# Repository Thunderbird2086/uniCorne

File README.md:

# uniCorne

uniCorne is inspired by [corne](foostatn/crkbd), and here are the key features of uniCorne:

1. **Controller Compatibility**: uniCorne is specifically tailored to work with ProMicro-like controllers such as [Nice!Nano](https://nicekeyboards.com/docs/nice-nano/), [Elite-Pi](https://docs.keeb.io/elite-pi-guide), and [Ble Micro Pro](https://sekigon-gonnoc.github.io/BLE-Micro-Pro/#/). This ensures seamless integration and optimal performance.
1. **Hardware Handedness**: Unlike many other keyboards, uniCorne supports hardware handedness for ProMicro-like RP2040 controller boards. This flexibility allows users to choose their preferred orientation without sacrificing functionality.
1. **Nice!View Integration**: uniCorne has been meticulously crafted to seamlessly integrate with [Nice!View](https://nicekeyboards.com/docs/nice-view/). Users can enjoy a cohesive experience without needing any modifications to the board.

In summary, uniCorne combines controller compatibility, hardware flexibility, and thoughtful integration, making it a standout choice for keyboard enthusiasts.

## Profiles
uniCorne offers three distinct flavors: standard profile, low profile, and hybrid profile.

### Standard Profile
Equipped with Cherry MX compatible switches, available in both 3-pin and 5-pin.<br>

### Low Profile
The low-profile variant primarily incorporates Kailh Low-Profile switches, supporting both Kailh Choc V1 and V2 switches.<br>

### Hybrid Profile
In the hybrid setup, low-profile switches are utilized for the thumb block, while standard-profile switches are employed for the remaining keys.<br>

## Variants
uniCorne is availabe in two enticing variations: 3x5 and 3x6.

The 3x6 variant caters to users who may not be accustomed to split keyboards, as its layout closely resembles that of standard keyboards. With 21 keys on each side, the 3x6 configuration boasts a total of 42 keys.<br>

On the other hand, the 3x5 variant provides a more streamlined option, with 18 keys on each side for a total of 36 keys.

## Build Guides
uniCorne 3x5 is used as an example. Refer to [the guides](https://thunderbird2086.github.io/uniCorne).

## fonts
 - [Android Robot](https://www.1001freefonts.com/android-robot.font)
 - [Avenir Next Heavy](https://en.maisfontes.com/avenir-next-heavy.font)
 - [Hack](https://www.1001freefonts.com/hack.font)

## firmwares
 - [QMK](https://github.com/Thunderbird2086/tb2086-qmk)
 - [ZMK](https://github.com/Thunderbird2086/unicorne-zmk-config)

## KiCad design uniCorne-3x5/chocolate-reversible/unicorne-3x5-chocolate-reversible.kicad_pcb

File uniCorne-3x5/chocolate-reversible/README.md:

# uniCorne 3x5 Low Profile

## Top

## Bottom

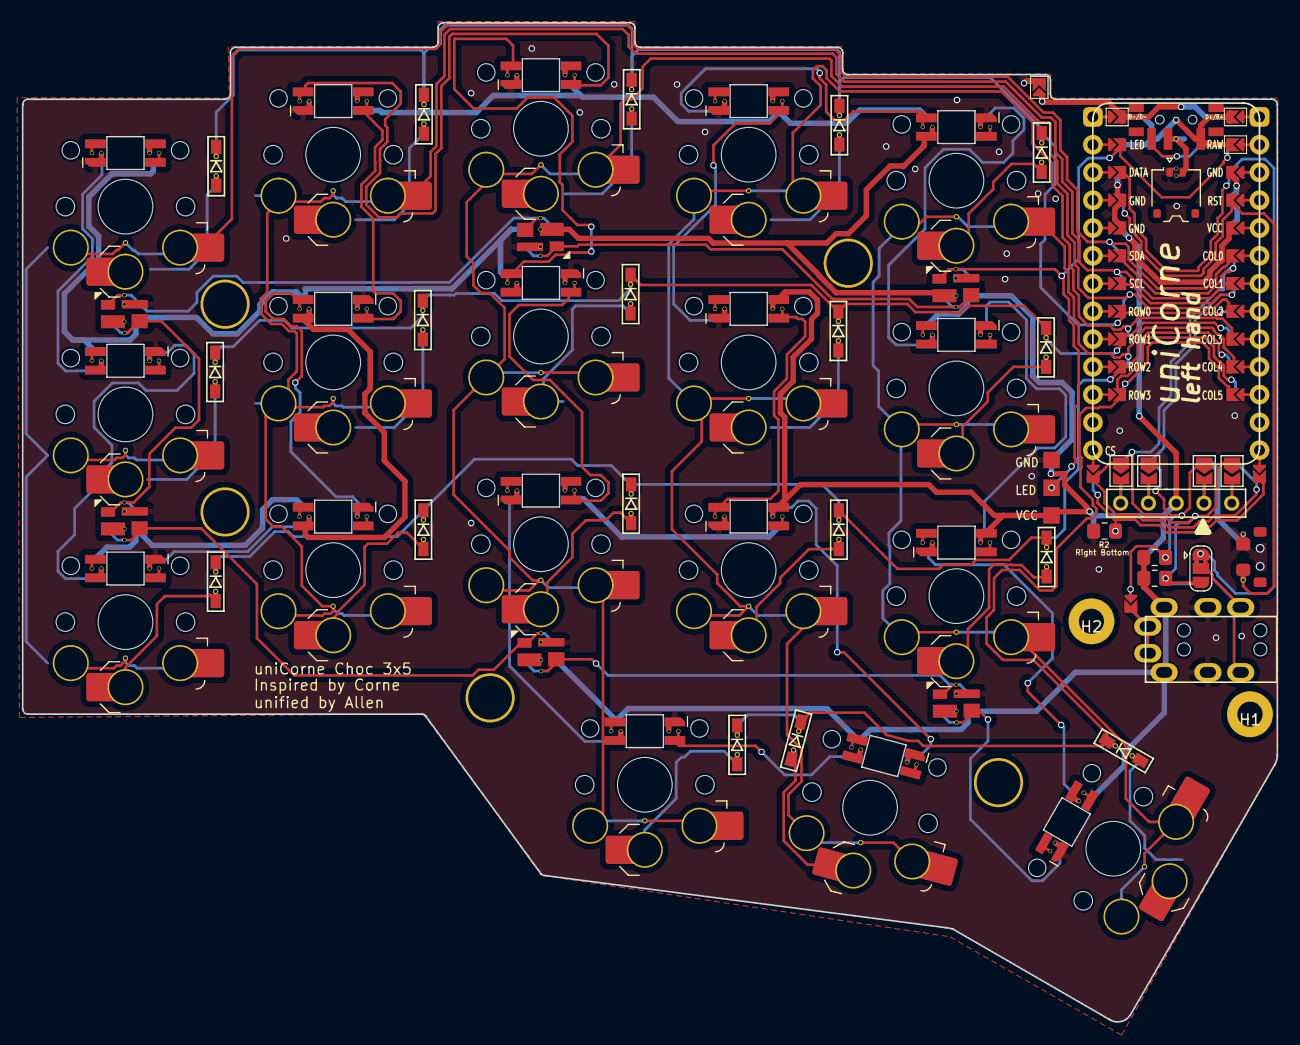
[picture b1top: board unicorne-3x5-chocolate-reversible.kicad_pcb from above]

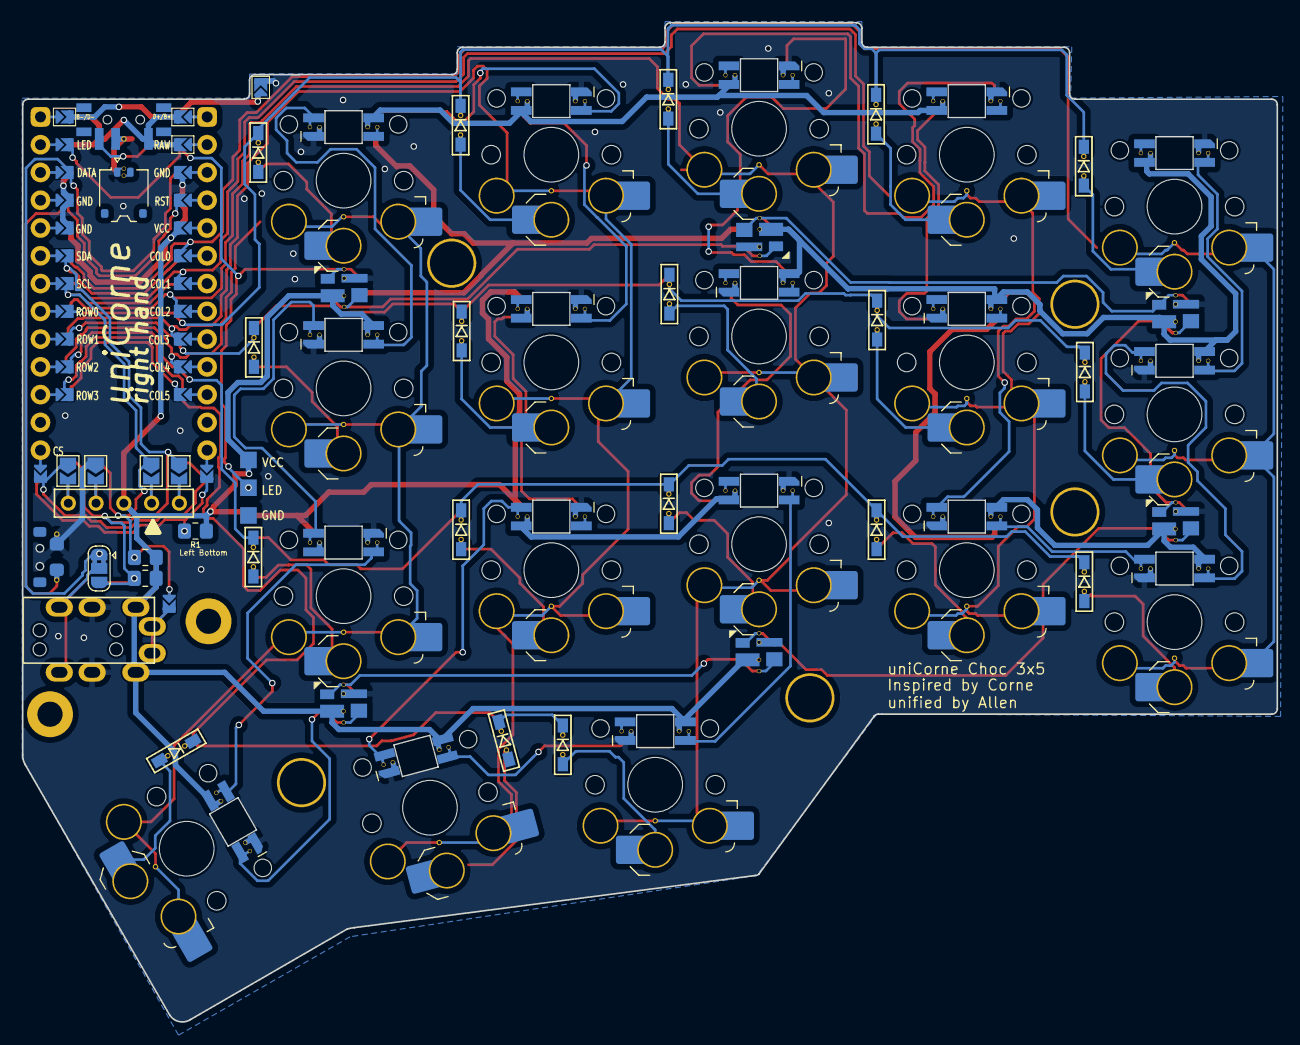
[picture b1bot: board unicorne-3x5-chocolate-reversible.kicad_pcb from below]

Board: 2 copper layers, 114.7 x 91.4 mm, 89 parts (30 on the bottom side), 68 nets.

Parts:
D1, D2, D3, D4, D5, D6, D7, D8, D9, D10, D11, D12, D13, D14, D15, D16, D17, D18: D; D3_SMD_rev
H1, H2: MountingHole; M2_Hole_TH
H3, H4, H5, H6, H7: MountingHole; M2_Hole_TH_Outside
J1: MJ-4PP-9; TRRS-PJ-320A-rev
J2: Conn_01x05; Nice!View
J3: Conn_01x02; Molex_Pico-EZmate_78171-0002_1x02-1MP_P1.20mm_Vertical_rev
J4: Conn_01x03; StripLED_rev
JP1, JP2, JP3, JP4, JP5, JP6, JP7, JP8: Jumper_2_Open; SolderJumper-2_P1.3mm_Open_TrianglePad1.0x1.5mm
JP9: Jumper_3_Bridged12; SolderJumper-3_P1.3mm_Bridged2Bar12_RoundedPad1.0x1.5mm_rev
JP10, JP11: SolderJumper-2_P1.3mm_Open_TrianglePad1.0x1.2mm_rev
L1, L2, L3, L4, L5, L6, L7, L8, L9, L10, L11, L12, L13, L14, L15, L16, L17, L18: SK6812MINI-E; LED_SK6812MINI-E_rev
L19, L20, L21, L22, L23, L24: SK6812MINI; LED_SK6812MINI_PLCC4_3.5x3.5mm_P1.75mm_rev_all
PSW1: SW_SPDT; SW_SPDT_PCM12_reversible
R1, R2: 10k; R_0805_2012Metric_Pad1.20x1.40mm_HandSolder
R3, R4: 4.7k; R_0805_2012Metric_Pad1.20x1.40mm_HandSolder_rev
RSW1: SMT 2X4X3.5MM Tactile Tact Push Button; SMT 2X4X3.5MM Tactile Tact Push Button rev
SW1, SW2, SW3, SW4, SW5, SW6, SW7, SW8, SW9, SW10, SW11, SW12, SW13, SW14, SW15, SW16, SW17: SW_CHOC_HS; SW_choc_v1_v2_HS_1u_reversible
SW18: SW_CHOC_HS; SW_choc_v1_v2_HS_1.5u_reversible
U1: ProMicro-ish; ProMicro-ish-dn-rev-unrouted_3x5

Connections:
B-/D-: JP11.1 (A), U1.26 (B-/D-)
BAT+: PSW1.1 (A), U1.24 (RAW), U1.25 (D+/B+)
CS: JP1.1 (A), JP8.1 (A), U1.12 (B5)
DATA: JP9.1 (A), U1.2 (RX)
GND: J1.C, J3.1, J4.1, JP2.1 (A), JP7.1 (A), JP11.2 (B), L1.3 (VSS), L2.3 (VSS), L3.3 (VSS), L4.3 (VSS), L5.3 (VSS), L6.3 (VSS), L7.3 (VSS), L8.3 (VSS), L9.3 (VSS), L10.3 (VSS), L11.3 (VSS), L12.3 (VSS), L13.3 (VSS), L14.3 (VSS), L15.3 (VSS), L16.3 (VSS), L17.3 (VSS), L18.3 (VSS), L19.2 (VSS), L20.2 (VSS), L21.2 (VSS), L22.2 (VSS), L23.2 (VSS), L24.2 (VSS), R2.1, RSW1.2, U1.3 (GND), U1.4 (GND), U1.23 (GND)
IS_LEFT: R1.2, R2.2, U1.13 (B6)
LED: J4.2, L21.3 (DIN), U1.1 (TX)
unnamed: D1.2 (A), SW1.2
unnamed: D2.2 (A), SW2.2
unnamed: D3.2 (A), SW3.2
unnamed: D4.2 (A), SW4.2
unnamed: D5.2 (A), SW5.2
unnamed: D6.2 (A), SW6.2
unnamed: D7.2 (A), SW7.2
unnamed: D8.2 (A), SW8.2
unnamed: D9.2 (A), SW9.2
unnamed: D10.2 (A), SW10.2
unnamed: D11.2 (A), SW11.2
unnamed: D12.2 (A), SW12.2
unnamed: D13.2 (A), SW13.2
unnamed: D14.2 (A), SW14.2
unnamed: D15.2 (A), SW15.2
unnamed: D16.2 (A), SW16.2
unnamed: D17.2 (A), SW17.2
unnamed: D18.2 (A), SW18.2
unnamed: J2.1, JP4.2 (B), JP8.2 (B)
unnamed: J2.2, JP3.2 (B), JP7.2 (B)
unnamed: J2.4, JP2.2 (B), JP6.2 (B)
unnamed: J2.5, JP1.2 (B), JP5.2 (B)
unnamed: J3.2, PSW1.2 (B)
unnamed: J1.B, JP9.2 (C)
unnamed: J1.A, JP10.2 (B)
unnamed: L1.4 (DIN), L6.2 (DOUT)
unnamed: L2.4 (DIN), L3.2 (DOUT)
unnamed: L2.2 (DOUT), L7.4 (DIN)
unnamed: L3.4 (DIN), L8.2 (DOUT)
unnamed: L4.4 (DIN), L5.2 (DOUT)
unnamed: L4.2 (DOUT), L9.4 (DIN)
unnamed: L10.4 (DIN), L15.2 (DOUT)
unnamed: L5.4 (DIN), L10.2 (DOUT)
unnamed: L11.4 (DIN), L12.2 (DOUT)
unnamed: L6.4 (DIN), L11.2 (DOUT)
unnamed: L7.2 (DOUT), L12.4 (DIN)
unnamed: L13.4 (DIN), L16.2 (DOUT)
unnamed: L8.4 (DIN), L13.2 (DOUT)
unnamed: L9.2 (DOUT), L14.4 (DIN)
unnamed: L14.2 (DOUT), L17.4 (DIN)
unnamed: L15.4 (DIN), L18.2 (DOUT)
unnamed: L16.4 (DIN), L17.2 (DOUT)
unnamed: L18.4 (DIN), L24.1 (DOUT)
unnamed: L19.3 (DIN), L20.1 (DOUT)
unnamed: L19.1 (DOUT), L22.3 (DIN)
unnamed: L20.3 (DIN), L21.1 (DOUT)
unnamed: L22.1 (DOUT), L23.3 (DIN)
unnamed: L23.1 (DOUT), L24.3 (DIN)
RESET: RSW1.1, U1.22 (RST)
SCL: JP3.1 (A), JP6.1 (A), JP10.1 (A), R3.1, U1.6 (SCL)
SDA: JP4.1 (A), JP5.1 (A), JP9.3 (B), R4.2, U1.5 (SDA)
VCC: J1.D, J2.3, J4.3, L1.1 (VDD), L2.1 (VDD), L3.1 (VDD), L4.1 (VDD), L5.1 (VDD), L6.1 (VDD), L7.1 (VDD), L8.1 (VDD), L9.1 (VDD), L10.1 (VDD), L11.1 (VDD), L12.1 (VDD), L13.1 (VDD), L14.1 (VDD), L15.1 (VDD), L16.1 (VDD), L17.1 (VDD), L18.1 (VDD), L19.4 (VDD), L20.4 (VDD), L21.4 (VDD), L22.4 (VDD), L23.4 (VDD), L24.4 (VDD), R1.1, R3.2, R4.1, U1.21 (VCC)
col0: SW1.1, SW6.1, SW11.1, U1.20 (F4)
col1: SW2.1, SW7.1, SW12.1, U1.19 (F5)
col2: SW3.1, SW8.1, SW13.1, SW16.1, U1.18 (F6)
col3: SW4.1, SW9.1, SW14.1, SW17.1, U1.17 (F7)
col4: SW5.1, SW10.1, SW15.1, SW18.1, U1.16 (B1)
row0: D1.1 (K), D2.1 (K), D3.1 (K), D4.1 (K), D5.1 (K), U1.7 (D4)
row1: D6.1 (K), D7.1 (K), D8.1 (K), D9.1 (K), D10.1 (K), U1.8 (C6)
row2: D11.1 (K), D12.1 (K), D13.1 (K), D14.1 (K), D15.1 (K), U1.9 (D7)
row3: D16.1 (K), D17.1 (K), D18.1 (K), U1.10 (E6)

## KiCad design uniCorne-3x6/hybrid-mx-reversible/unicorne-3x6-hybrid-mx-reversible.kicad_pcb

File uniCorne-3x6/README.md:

# uniCorne 3x6

* cherry-mx-reversible : Standard Profile<br>

* chocolate-reversible : Low Profile<br>

* mybrid-mx-reversible : Hybrid Profile<br>

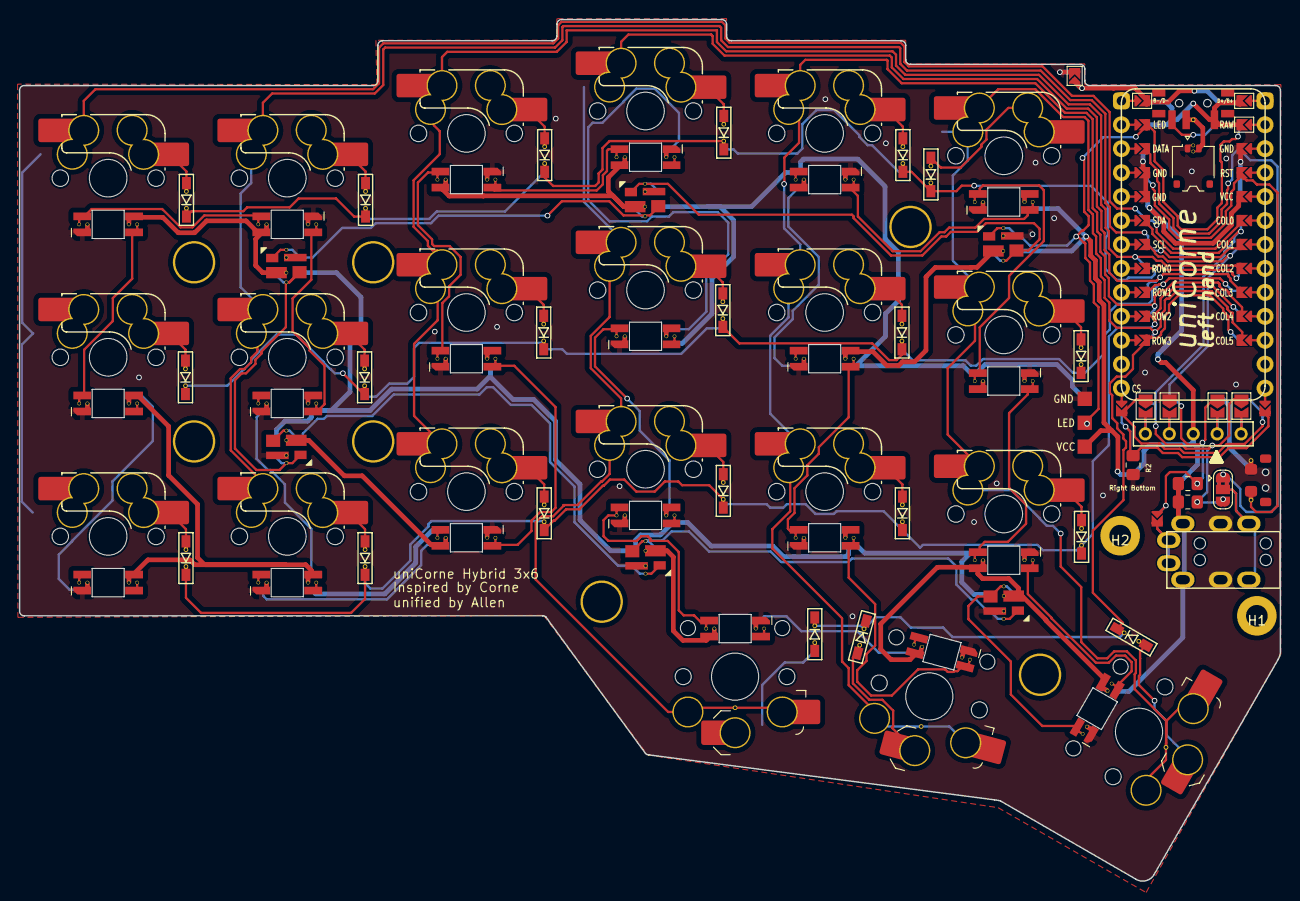
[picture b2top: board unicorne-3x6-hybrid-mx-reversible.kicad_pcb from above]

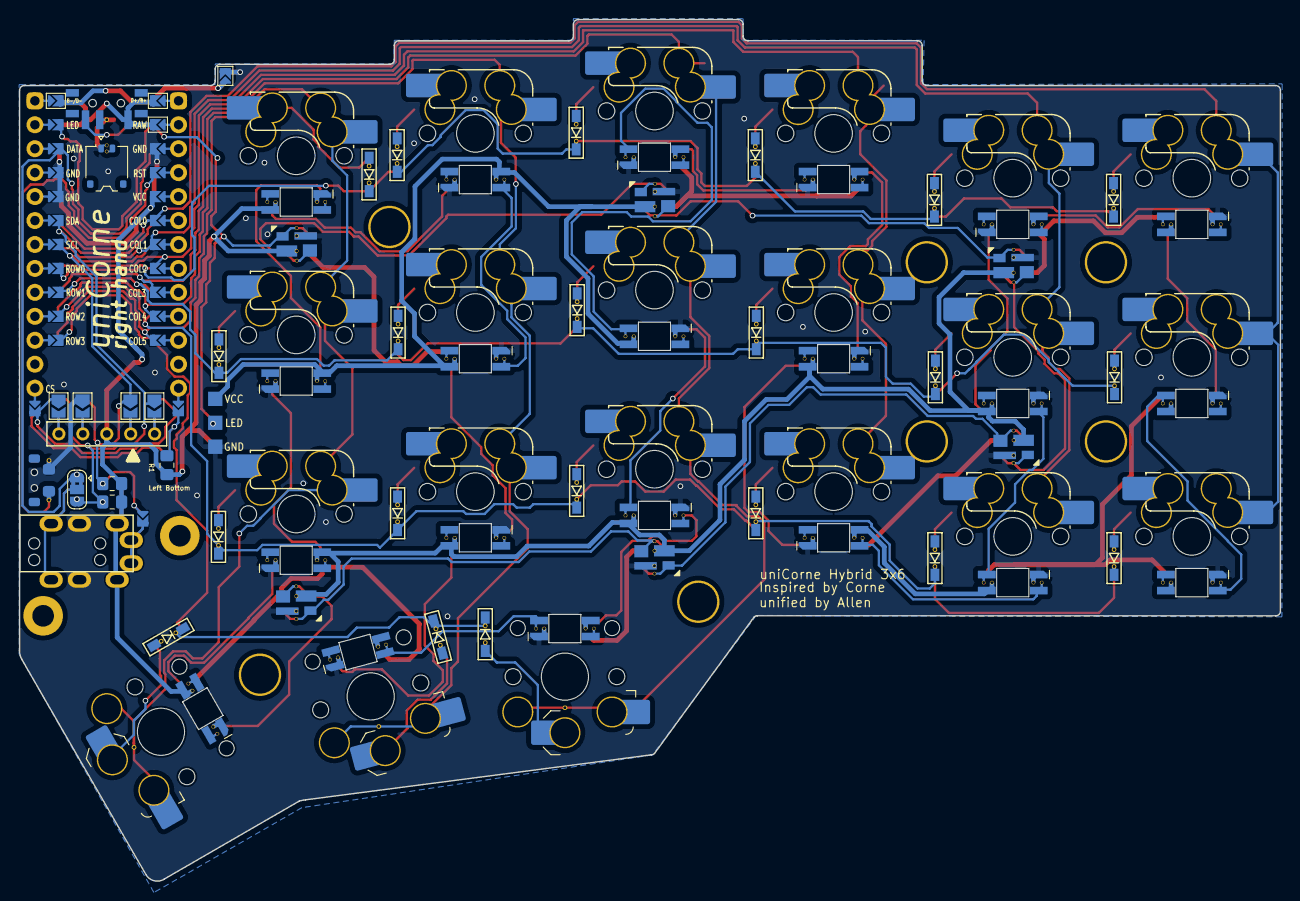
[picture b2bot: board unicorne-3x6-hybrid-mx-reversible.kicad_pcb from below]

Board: 2 copper layers, 133.8 x 91.4 mm, 100 parts (33 on the bottom side), 75 nets.

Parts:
D1, D2, D3, D4, D5, D6, D7, D8, D9, D10, D11, D12, D13, D14, D15, D16, D17, D18, D19, D20, D21: D; D3_SMD_rev
H1, H2: MountingHole; M2_Hole_TH
H3, H4, H5, H6, H7, H8, H9: MountingHole; M2_Hole_TH_Outside
J1: MJ-4PP-9; TRRS-PJ-320A-rev
J2: Nice!View
J3: Conn_01x02; Molex_Pico-EZmate_78171-0002_1x02-1MP_P1.20mm_Vertical_rev
J4: Conn_01x03; StripLED_rev
JP1, JP2, JP3, JP4, JP5, JP6, JP7, JP8: SolderJumper-2_P1.3mm_Open_TrianglePad1.0x1.5mm
JP9, JP11: SolderJumper-2_P1.3mm_Open_TrianglePad1.0x1.2mm_rev
JP10: Jumper_3_Bridged12; SolderJumper-3_P1.3mm_Bridged2Bar12_RoundedPad1.0x1.5mm_rev
L1, L2, L3, L4, L5, L6, L7, L8, L9, L10, L11, L12, L13, L14, L15, L16, L17, L18, L19, L20, L21: SK6812MINI-E; LED_SK6812MINI-E_rev
L22, L23, L24, L25, L26, L27: SK6812MINI; LED_SK6812MINI_PLCC4_3.5x3.5mm_P1.75mm_rev_all
PSW1: SW_SPDT; SW_SPDT_PCM12_reversible
R1, R2: 10k; R_0805_2012Metric_Pad1.20x1.40mm_HandSolder
R3, R4: 4.7k; R_0805_2012Metric_Pad1.20x1.40mm_HandSolder_rev
RSW1: SW_PUSH; SMT 2X4X3.5MM Tactile Tact Push Button rev
SW1, SW2, SW3, SW4, SW5, SW6, SW7, SW8, SW9, SW10, SW11, SW12, SW13, SW14, SW15, SW16, SW17, SW18: SW_MX_HS; SW_MX_HS_1u_reversible
SW19: SW_CHOC_HS; SW_choc_v1_v2_HS_1u_reversible
SW20, SW21: SW_CHOC_HS; SW_choc_v1_v2_HS_1.5u_reversible
U1: ProMicro-ish; ProMicro-ish-dn-rev-unrouted_3x6

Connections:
B-/D-: JP11.1 (A), U1.26 (B-/D-)
BAT+: PSW1.1 (A), U1.24 (RAW), U1.25 (D+/B+)
CS: JP1.1 (A), JP8.1 (A), U1.12 (B5)
DATA: JP10.1 (A), U1.2 (RX)
GND: J1.C, J3.1, J4.1, JP2.1 (A), JP7.1 (A), JP11.2 (B), L1.3 (VSS), L2.3 (VSS), L3.3 (VSS), L4.3 (VSS), L5.3 (VSS), L6.3 (VSS), L7.3 (VSS), L8.3 (VSS), L9.3 (VSS), L10.3 (VSS), L11.3 (VSS), L12.3 (VSS), L13.3 (VSS), L14.3 (VSS), L15.3 (VSS), L16.3 (VSS), L17.3 (VSS), L18.3 (VSS), L19.3 (VSS), L20.3 (VSS), L21.3 (VSS), L22.2 (VSS), L23.2 (VSS), L24.2 (VSS), L25.2 (VSS), L26.2 (VSS), L27.2 (VSS), R2.1, RSW1.1, U1.3 (GND), U1.4 (GND), U1.23 (GND)
IS_LEFT: R1.2, R2.2, U1.13 (B6)
LED: J4.2, L24.3 (DIN), U1.1 (TX)
unnamed: D1.2 (A), SW1.2
unnamed: D2.2 (A), SW2.2
unnamed: D3.2 (A), SW3.2
unnamed: D4.2 (A), SW4.2
unnamed: D5.2 (A), SW5.2
unnamed: D6.2 (A), SW6.2
unnamed: D7.2 (A), SW7.2
unnamed: D8.2 (A), SW8.2
unnamed: D9.2 (A), SW9.2
unnamed: D10.2 (A), SW10.2
unnamed: D11.2 (A), SW11.2
unnamed: D12.2 (A), SW12.2
unnamed: D13.2 (A), SW13.2
unnamed: D14.2 (A), SW14.2
unnamed: D15.2 (A), SW15.2
unnamed: D16.2 (A), SW16.2
unnamed: D17.2 (A), SW17.2
unnamed: D18.2 (A), SW18.2
unnamed: D19.2 (A), SW19.2
unnamed: D20.2 (A), SW20.2
unnamed: D21.2 (A), SW21.2
unnamed: J2.1, JP4.2 (B), JP8.2 (B)
unnamed: J2.2, JP3.2 (B), JP7.2 (B)
unnamed: J2.4, JP2.2 (B), JP6.2 (B)
unnamed: J2.5, JP1.2 (B), JP5.2 (B)
unnamed: J3.2, PSW1.2 (B)
unnamed: J1.A, JP9.2 (B)
unnamed: J1.B, JP10.2 (C)
unnamed: L1.4 (DIN), L2.2 (DOUT)
unnamed: L1.2 (DOUT), L7.4 (DIN)
unnamed: L2.4 (DIN), L8.2 (DOUT)
unnamed: L3.4 (DIN), L4.2 (DOUT)
unnamed: L3.2 (DOUT), L9.4 (DIN)
unnamed: L5.4 (DIN), L6.2 (DOUT)
unnamed: L10.4 (DIN), L16.2 (DOUT)
unnamed: L4.4 (DIN), L10.2 (DOUT)
unnamed: L5.2 (DOUT), L11.4 (DIN)
unnamed: L11.2 (DOUT), L17.4 (DIN)
unnamed: L12.4 (DIN), L18.2 (DOUT)
unnamed: L6.4 (DIN), L12.2 (DOUT)
unnamed: L7.2 (DOUT), L13.4 (DIN)
unnamed: L14.4 (DIN), L15.2 (DOUT)
unnamed: L8.4 (DIN), L14.2 (DOUT)
unnamed: L9.2 (DOUT), L15.4 (DIN)
unnamed: L16.4 (DIN), L19.2 (DOUT)
unnamed: L17.2 (DOUT), L20.4 (DIN)
unnamed: L18.4 (DIN), L21.2 (DOUT)
unnamed: L19.4 (DIN), L20.2 (DOUT)
unnamed: L21.4 (DIN), L27.1 (DOUT)
unnamed: L22.3 (DIN), L23.1 (DOUT)
unnamed: L22.1 (DOUT), L25.3 (DIN)
unnamed: L23.3 (DIN), L24.1 (DOUT)
unnamed: L25.1 (DOUT), L26.3 (DIN)
unnamed: L26.1 (DOUT), L27.3 (DIN)
RESET: RSW1.2, U1.22 (RST)
SCL: JP3.1 (A), JP6.1 (A), JP9.1 (A), R3.1, U1.6 (SCL)
SDA: JP4.1 (A), JP5.1 (A), JP10.3 (B), R4.2, U1.5 (SDA)
VCC: J1.D, J2.3, J4.3, L1.1 (VDD), L2.1 (VDD), L3.1 (VDD), L4.1 (VDD), L5.1 (VDD), L6.1 (VDD), L7.1 (VDD), L8.1 (VDD), L9.1 (VDD), L10.1 (VDD), L11.1 (VDD), L12.1 (VDD), L13.1 (VDD), L14.1 (VDD), L15.1 (VDD), L16.1 (VDD), L17.1 (VDD), L18.1 (VDD), L19.1 (VDD), L20.1 (VDD), L21.1 (VDD), L22.4 (VDD), L23.4 (VDD), L24.4 (VDD), L25.4 (VDD), L26.4 (VDD), L27.4 (VDD), R1.1, R3.2, R4.1, U1.21 (VCC)
col0: SW1.1, SW7.1, SW13.1, U1.20 (F4)
col1: SW2.1, SW8.1, SW14.1, U1.19 (F5)
col2: SW3.1, SW9.1, SW15.1, U1.18 (F6)
col3: SW4.1, SW10.1, SW16.1, SW19.1, U1.17 (F7)
col4: SW5.1, SW11.1, SW17.1, SW20.1, U1.16 (B1)
col5: SW6.1, SW12.1, SW18.1, SW21.1, U1.15 (B3)
row0: D1.1 (K), D2.1 (K), D3.1 (K), D4.1 (K), D5.1 (K), D6.1 (K), U1.7 (D4)
row1: D7.1 (K), D8.1 (K), D9.1 (K), D10.1 (K), D11.1 (K), D12.1 (K), U1.8 (C6)
row2: D13.1 (K), D14.1 (K), D15.1 (K), D16.1 (K), D17.1 (K), D18.1 (K), U1.9 (D7)
row3: D19.1 (K), D20.1 (K), D21.1 (K), U1.10 (E6)

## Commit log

2024-01-13 Top plate - PCB
2024-01-14 amend PCB
2024-01-15 amend silkscreen
2024-01-21 hybrid
2024-02-02 hardware handedness
2024-02-03 small tweak
2024-02-03 add kiplot
2024-02-03 added bottom plate
2024-02-04 amend cases
2024-02-05 reorg structure
2024-02-06 uniCorne 3x6 cherry-mx
2024-02-06 uniCorne 3x6 chocolate
2024-02-06 uniCorne 3x6 hybrid
2024-02-07 Amended hybrid 3x6
2024-02-07 amended hybrid 3x5
2024-02-07 amended cherry mx 3x5
2024-02-07 amended chocolate 3x5
2024-02-09 added plates
2024-02-10 amended cases
2024-02-11 fix typo
2024-02-15 added case for 3x6
2024-02-18 added github actions
2024-02-25 amended footprint for LED
2024-03-02 added fonts
2024-03-02 added fonts (#1)
2024-03-03 fixed footprint for promicro-ish 3x6
2024-03-09 added more README
2024-03-31 Documents (#2)
    * Update README.md
    * added more README
2024-06-16 fixed 3x5 hyprid mx
2024-06-17 fixed 3x5
2024-06-17 fixed 3x6
2024-06-17 Bug fix scl (#3)
    * fixed 3x5 hyprid mx
    * fixed 3x5
    * fixed 3x6
2024-09-19 added fusion files
2024-09-19 added fusion files (#4)
2024-10-02 added build guide
2024-10-02 correct link
2024-10-02 Docs (#5)
    * added build guide
    * correct link
2024-10-02 fixed typo
2024-10-02 fixed typo (#6)
2024-10-02 added theme
2024-10-02 added theme (#7)
2024-10-02 updated title
2024-10-02 updated title (#8)
2024-10-02 fixed broken table
2024-10-02 fixed broken table (#9)
2024-10-04 resize images
2024-10-04 resize images (#10)
2024-10-06 updated build guide
2024-10-06 Added the link for github doc
2024-10-06 Docs (#11)
    * updated build guide
    * Added the link for github doc
2024-10-25 KiCAD 8
2024-10-25 KiCad8 for plates
2024-10-26 Update Footprints
2024-10-26 added more docs
2024-10-26 Docs / KiCad8 (#12)
    * KiCAD 8
    * KiCad8 for plates
    * Update Footprints
    * Update README.md
    * added more docs
2024-10-29 updated submodule
2026-02-16 fixed SDA/SCL shorted
2026-02-16 fixed workflows
2026-02-16 KiCad v2_k9
2026-02-16 fixed SDA/SCL shorted (#15)
    * fixed SDA/SCL shorted
    * fixed workflows
    * KiCad v2_k9
